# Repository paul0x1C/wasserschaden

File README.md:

# wasserschaden
Project to control solenoid valves over mqtt, check each nodes status in a webpage and via Grafana. 
It allows you to set a location for each node that connects for the first time for easier maintenance.
Nodes equipped with a temperature sensor also send temperature information via mqtt.
To prevent two solenoid valves opening simultaniously, a house enters "locked state". Before opening a solenoid valve,
it checks the lockstate of its house and will only open if the house is in unlocked state.
We log every opening and closing of a valve in order to be able to generate a csv log file, to prove reliability.

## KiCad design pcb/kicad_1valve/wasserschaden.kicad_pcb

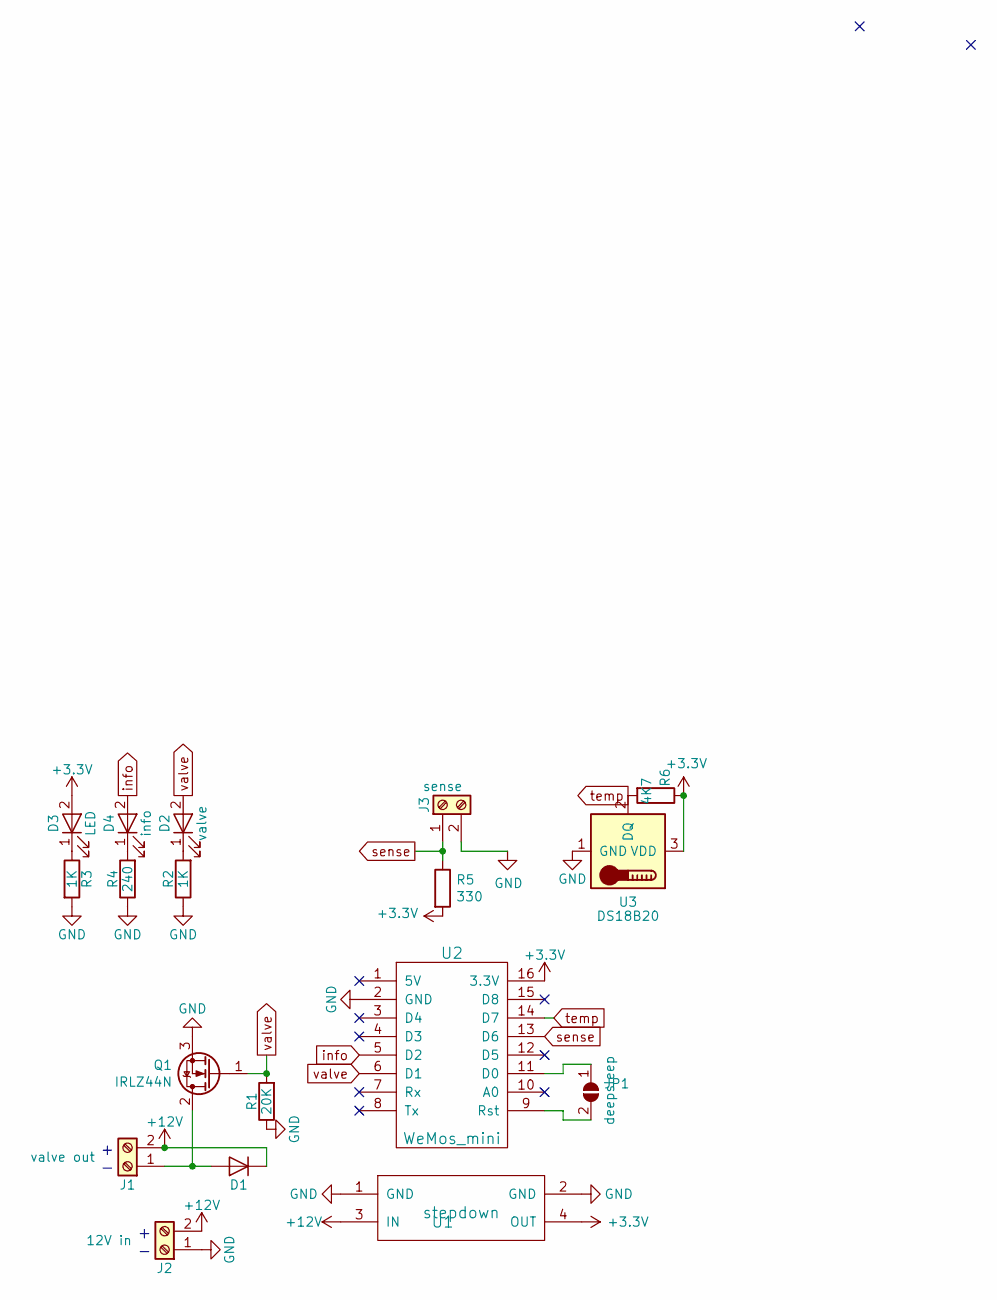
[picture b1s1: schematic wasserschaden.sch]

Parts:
D1: D_SMA_Handsoldering
D2: valve; LED_D3.0mm
D3: LED; LED_D3.0mm
D4: info; LED_D3.0mm
J1: valve out; termina_2pin
J2: 12V in; termina_2pin
J3: sense; termina_2pin
JP1: deepsleep; jumper
Q1: IRLZ44N; TO-220-3_Vertical
R1: 20K; R_0603_HandSoldering
R2, R3: 1K; R_0603_HandSoldering
R4: 240; R_0603_HandSoldering
R5: 330; R_0603_HandSoldering
R6: 4K7; R_0603_HandSoldering
U1: stepdown
U2: WeMos_mini; wemos
U3: DS18B20; temperature_sensor

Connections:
+3V3: D3.2 (A), R5.2, R6.1, U1.4 (OUT), U2.16 (3.3V), U3.3 (VDD)
+12V: D1.1 (K), J1.2, J2.2, U1.3 (IN)
GND: J2.1, J3.2, Q1.3 (S), R1.1, R2.1, R3.2, R4.1, U1.1 (GND), U1.2 (GND), U2.2 (GND), U3.1 (GND); also elsewhere on the board
unnamed 3: D1.2 (A), J1.1, Q1.2 (D); also elsewhere on the board
unnamed: D2.1 (K), R2.2
unnamed: D3.1 (K), R3.1
unnamed: D4.1 (K), R4.2
unnamed: JP1.1 (A), U2.11 (D0)
unnamed: JP1.2 (B), U2.9 (Rst)
info: D4.2 (A), U2.5 (D2)
sense: J3.1, R5.1, U2.13 (D6)
temp: R6.2, U2.14 (D7), U3.2 (DQ)
valve: D2.2 (A), Q1.1 (G), R1.2, U2.6 (D1); also elsewhere on the board

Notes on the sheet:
+ -

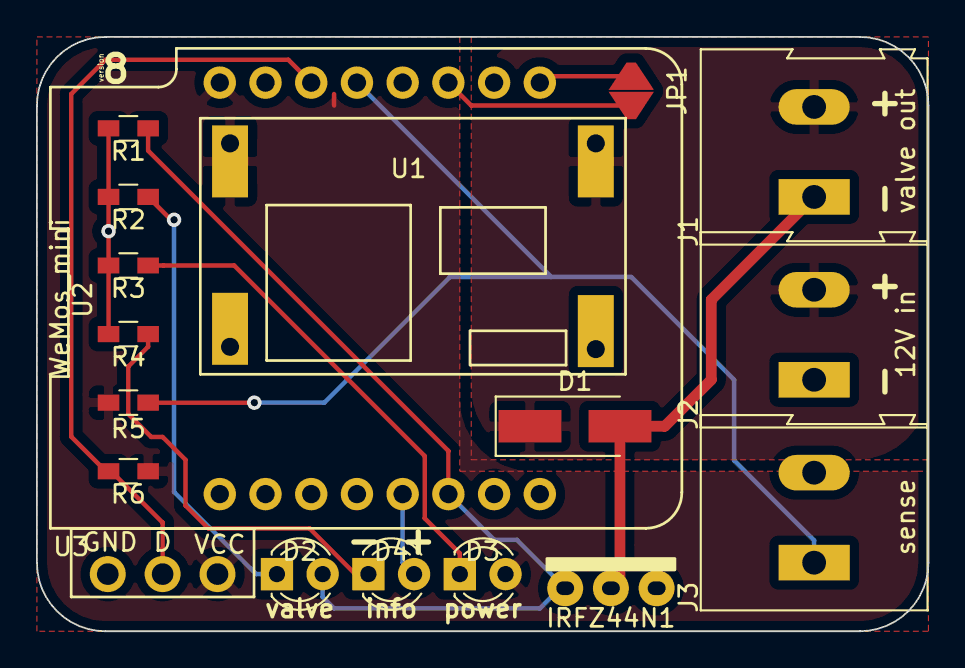
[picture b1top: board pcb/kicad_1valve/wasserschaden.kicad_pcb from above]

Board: 2 copper layers, 49.5 x 33.0 mm, 18 parts (0 on the bottom side), 13 nets.

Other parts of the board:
IRFZ44N1: irlz44n_vertical

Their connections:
GND: IRFZ44N1.1; also elsewhere on the board
unnamed 3: IRFZ44N1.3; also elsewhere on the board
valve: IRFZ44N1.2; also elsewhere on the board

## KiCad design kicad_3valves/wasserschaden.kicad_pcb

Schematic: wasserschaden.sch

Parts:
D1: LED; LED_D3.0mm
D2: info; LED_D3.0mm
D3: v1; LED_D3.0mm
D4: v2; LED_D3.0mm
D5, D7, D8: D_SMA_Handsoldering
D6: v3; LED_D3.0mm
IRFZ44N1, IRFZ44N2, IRFZ44N3: irlz44n_vertical
J1: v1 out; termina_2pin
J2: 12V in; termina_2pin
J3: sense; termina_2pin
J4: v2 out; termina_2pin
J5: v3 out; termina_2pin
JP1: deepsleep; jumper
R1, R3, R4, R6: 1K; R_0603_HandSoldering
R2: 240; R_0603_HandSoldering
R5, R9, R10: 20K; R_0603_HandSoldering
R7: 330; R_0603_HandSoldering
R8: 4K7; R_0603_HandSoldering
U1: stepdown
U2: WeMos_mini; wemos
U3: DS18B20; temperature_sensor

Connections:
+3V3: D1.2 (A), R7.2, R8.1, U1.4, U2.16 (3.3V), U3.3 (VDD)
+12V: D5.1 (K), D7.1 (K), D8.1 (K), J1.2, J2.2, J4.2, J5.2, U1.3
GND: J2.1, J3.2, R1.2, R2.1, R3.1, R4.1, R5.1, R6.1, R9.1, R10.1, U1.1, U1.2, U2.2 (GND), U3.1 (GND); also elsewhere on the board
unnamed: D1.1 (K), R1.1
unnamed: D2.1 (K), R2.2
unnamed: D3.1 (K), R3.2
unnamed: D4.1 (K), R4.2
unnamed 7: D5.2 (A), J1.1; also elsewhere on the board
unnamed: D6.1 (K), R6.2
unnamed 9: D7.2 (A), J4.1; also elsewhere on the board
unnamed 10: D8.2 (A), J5.1; also elsewhere on the board
unnamed: JP1.1 (A), U2.11 (D0)
unnamed: JP1.2 (B), U2.9 (Rst)
info: D2.2 (A), U2.5 (D2)
sense: J3.1, R7.1, U2.13 (D6)
temp: R8.2, U2.14 (D7), U3.2 (DQ)
v1: D3.2 (A), R5.2, U2.6 (D1); also elsewhere on the board
v2: D4.2 (A), R9.2, U2.12 (D5); also elsewhere on the board
v3: D6.2 (A), R10.2, U2.15 (D8); also elsewhere on the board

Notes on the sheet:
+ -

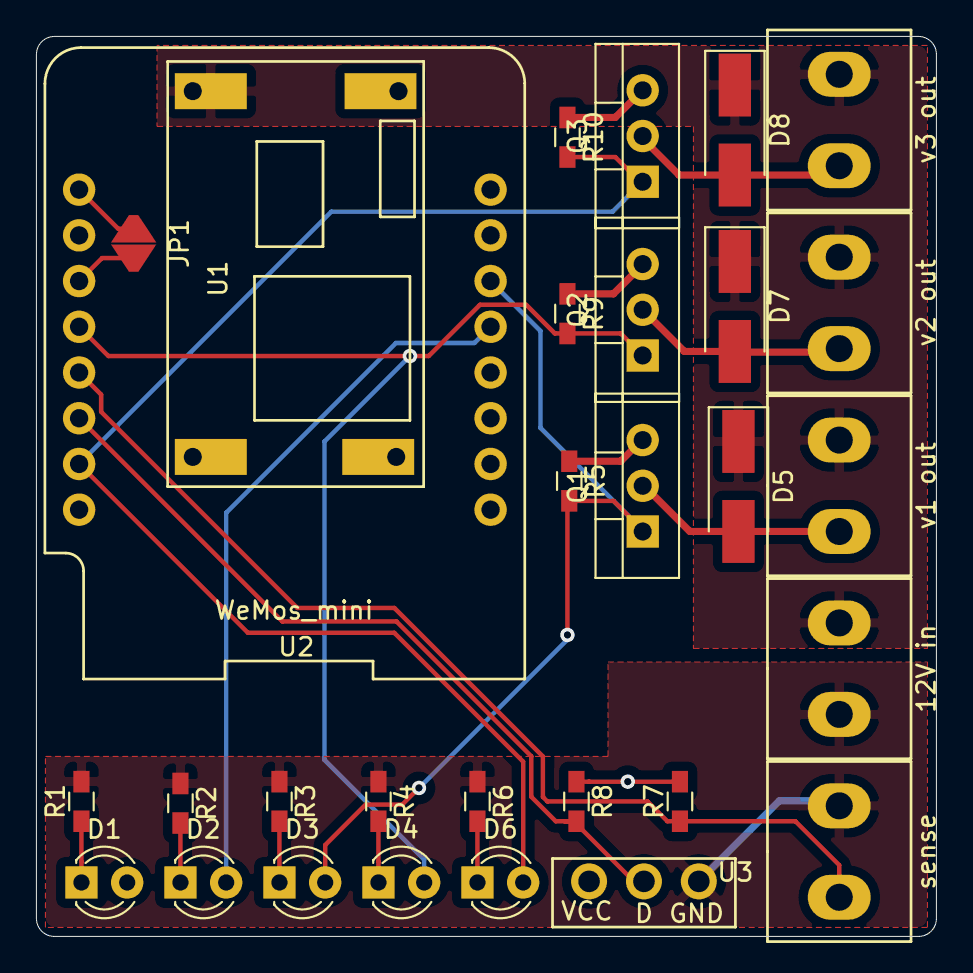
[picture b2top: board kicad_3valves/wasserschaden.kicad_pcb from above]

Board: 2 copper layers, 50.0 x 50.0 mm, 30 parts (0 on the bottom side), 19 nets.

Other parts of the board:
Q1, Q2, Q3: IRLZ44N; TO-220-3_Vertical

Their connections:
GND: Q1.3, Q2.3, Q3.3; also elsewhere on the board
unnamed 7: Q1.2; also elsewhere on the board
unnamed 9: Q2.2; also elsewhere on the board
unnamed 10: Q3.2; also elsewhere on the board
v1: Q1.1; also elsewhere on the board
v2: Q2.1; also elsewhere on the board
v3: Q3.1; also elsewhere on the board

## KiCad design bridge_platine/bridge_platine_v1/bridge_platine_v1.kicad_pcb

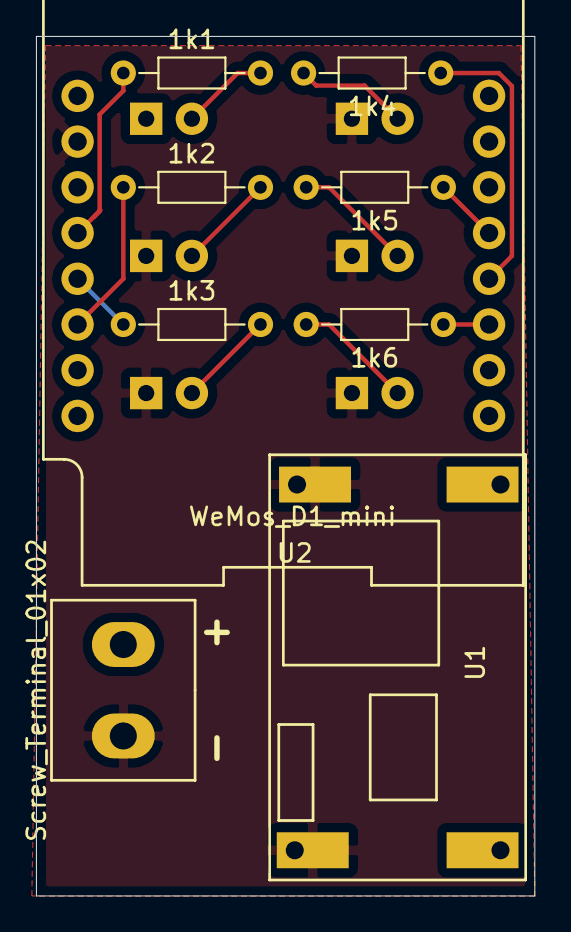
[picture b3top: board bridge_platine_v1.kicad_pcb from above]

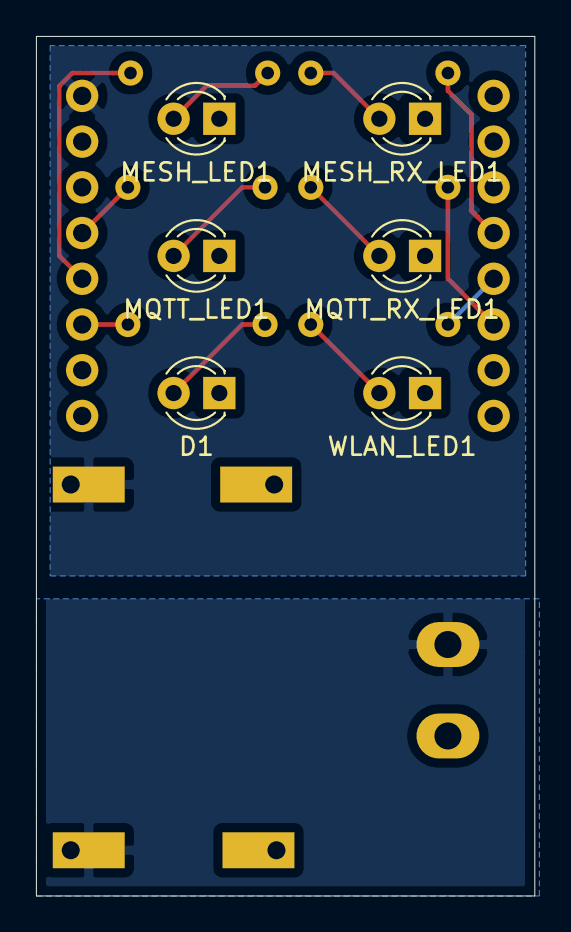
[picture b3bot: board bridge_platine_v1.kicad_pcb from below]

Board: 2 copper layers, 27.7 x 47.8 mm, 15 parts (6 on the bottom side), 15 nets.

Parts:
1k1, 1k2, 1k3, 1k4, 1k5, 1k6: R; R_Axial_DIN0204_L3.6mm_D1.6mm_P7.62mm_Horizontal
D1: POWER_LED; LED_D3.0mm
J1: Screw_Terminal_01x02; termina_2pin
MESH_LED1: LED; LED_D3.0mm
MESH_RX_LED1: LED; LED_D3.0mm
MQTT_LED1: LED; LED_D3.0mm
MQTT_RX_LED1: LED; LED_D3.0mm
U1: stepdown-wasserschaden-cache-2018-10-17-20-35-24; stepdown
U2: WeMos_D1_mini; wemos
WLAN_LED1: LED; LED_D3.0mm

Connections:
+3V3: U1.4, U2.8
GND: D1.1, J1.2, MESH_LED1.1, MQTT_LED1.1, MQTT_RX_LED1.1, U1.1, U1.2, U2.10, WLAN_LED1.1
unnamed: 1k1.1, U2.12
unnamed: 1k1.2, MESH_RX_LED1.2
unnamed: 1k2.1, U2.14
unnamed: 1k2.2, MQTT_RX_LED1.2
unnamed: 1k3.1, U2.13
unnamed: 1k3.2, WLAN_LED1.2
unnamed: 1k4.1, U2.4
unnamed: 1k4.2, MESH_LED1.2
unnamed: 1k5.1, U2.5
unnamed: 1k5.2, MQTT_LED1.2
unnamed: 1k6.1, U2.3
unnamed: 1k6.2, D1.2
unnamed: J1.1, U1.3

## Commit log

2018-08-20 added key.py to gitignore
2018-08-21 better new node handeling and more featurs in node_info.html
2018-08-24 auto refresh
2018-08-26 splited loop.py in timer_loop.py and mqtt_loop.py; fixed automatic mqtt reconnect
2018-08-26 handle advanced ping messages
2018-08-26 added auto refresh options in html
2018-08-26 added autorefresh on/off switch
2018-08-26 added ardunio files to repo
2018-08-26 removed old files
2018-08-29 small fixes
2018-09-22 added log message
2018-09-22 small testing changes
2018-09-26 not sending ping to nodes on first connection
2018-09-26 utf 8 encoding
2018-09-26 db charset
2018-10-01 added status leds
2018-10-01 added caseplans
2018-10-05 implemented status leds
2018-10-10 implemented mqtt custom topics
2018-10-10 custom mqtt topic
2018-10-10 Revert "custom mqtt topic"
    This reverts commit 6651eda04687c469d4528e4c1a76eaf6a2c9868e.
2018-10-10 no flushing when interval=0
2018-10-10 string fuu
2018-10-10 Revert "string fuu"
    This reverts commit 82bc943778d458de0eda92c456a078fc5ff517e1.
2018-10-10 string fck ups
2018-10-13 removed unused functions
2018-10-15 bugfixes
2018-10-17 edit house feature
2018-10-17 less ping spaming when node is diconnected for a long time
2018-10-17 last will
2018-10-17 added kicad files
2018-10-17 queue length indication
2018-10-17 csv export
2018-10-17 clear queue button
2018-10-21 auto updates without stupid refreshes every second ;)
2018-10-21 removed debug console.log()
2018-10-21 fixed decorators
2018-10-22 moved delete options to extra page
2018-10-22 use for new nodes button
2018-10-22 autorefresh when new node is connected
2018-10-22 some cleanup
2018-10-22 new states
2018-10-22 New state colors
2018-10-22 Added BorderColor
2018-10-22 now use two states (connection, physical) instead of one
2018-10-22 mqtt logging
2018-10-22 reactivated reports & node_info
2018-10-23 moved node functions from actions.py to node class
2018-10-24 renamed length to duration
2018-10-24 added deepsleep jumper to schematic &cleanup
2018-10-24 moved caseplans to own folder
2018-10-24 fake mesh for testing base
2018-10-24 working fakemesh with 300 nodes
2018-10-24 removed test.html
2018-10-24 added more log messages
2018-10-26 added next flush info to website
2018-10-26 performance optim.: check only nodes that are not closed and connected
2018-10-26 performance optimization: locks
2018-10-28 css refactored
2018-10-28 added house_id to queue
2018-10-28 added missing session argument
2018-10-28 fixed system module update function
2018-11-01 adjusted alert string size
2018-11-02 added python requirements
2018-11-02 moved node state change to models
2018-11-02 change db to localhost
2018-11-02 react to broadcasts
2018-11-02 performance optimizazion with smarte queue checking
2018-11-02 logging, function names, comments
2018-11-03 comments, logging
2018-11-03 new_node_flat now selectable for each house
2018-11-03 added telegrambot
2018-11-03 changed length to duration
2018-11-03 added missing >
2018-11-03 prevent houses from not beeing unlocked
2018-11-05 small adjustments
2018-11-05 Added representers
2018-11-05 now using new representers
2018-11-08 moved node state change to timer_loop, added workaround for relationship bug
2018-11-08 added watchdog
2018-11-08 added watchdog, fixed bug with custom bridge topics
2018-11-09 moved house unlocking to mqtt loop
2018-11-09 prevent requeueing of nodes
2018-11-09 added jumper to pcb
2018-11-10 added sense jumper to schematic
2018-11-10 small optimizzations
2018-11-10 added priority levels to add_alert function
2018-11-10 added alert priority to telegram bot
2018-11-11 Update LICENSE
2018-11-12 made gateway pingable
2018-11-12 removed test line that broke priority checking
2018-11-12 added 'not conneceted' msg haneling
2018-11-12 cleaned up kicad dir
2018-11-12 fakemesh with 6 different gateways
2018-11-12 added sense input
2018-11-12 major pcb rearangement
2018-11-12 chagned gateway_status to int, added alert emojis, moved chat_id to key.py
2018-11-12 added msg length limit for telegram messages
2018-11-12 changed datetime string representation on website
2018-11-12 combine repeating alerts
2018-11-12 created ping function for Node, more bot options
2018-11-12 better bot menu
2018-11-12 added alert on requeueing of nodes
2018-11-13 added button selection for priority levels
2018-11-13 send not connected from node, when node is not connected
2018-11-13 pcb redesigen
2018-11-28 enabled watchdog, changed flushtime, reboot if bridge is not found
2018-11-28 added function to calc average resp. time
2018-12-01 added log function, globally replaced logger
2018-12-01 fixed timer_loop failing when last_flush is not set
2018-12-05 added led test on boot
2018-12-06 commit session after locking house
2018-12-06 only process que if qateway is connected
2018-12-06 added temperature sensor
2018-12-08 added R values, improved stepdown footprint, rerouted resistors
2019-01-10 added temperature and water sense, updated communication
2019-01-13 updated fakemesh to new communication
2019-01-13 nicer silkscreen
2019-01-13 updated communication, added temperature sensror, set root node
2019-01-13 don't spam gateway pings
2019-01-17 use utc time in db
2019-01-17 connection state names changed
2019-01-17 better gateway state handeling
2019-01-24 fixed deleting and moving nodes
2019-01-24 Created a readme file with project overview
2019-01-24 changed wording
2019-01-31 run one wire on the right pin ^^
2019-01-31 added 12V zone, made screw terminals interlockable
2019-02-07 added more comments
2019-02-08 first smd version
2019-02-08 v4 export
2019-02-14 small rerouting
2019-02-24 fixed minor mistakes
2019-02-25 fixed time stuff
2019-02-25 added node stats for houses
2019-02-25 added watchdog, changed mqtt ip, set wifi mode & channel
2019-02-25 formating fix
2019-02-27 added tempeature polling
2019-02-27 prevent temperature request spamming
2019-02-27 fixed circular dep. error when deleting houses
2019-04-09 pcb v7
2019-04-09 multi gateway support
2019-04-09 added temperature sensor reset option
2019-04-09 removed small important mistakes
2019-04-16 fixed traces near pads
2019-04-16 removed old zip
2019-05-06 added 3d design for valves on HT pipe
2019-05-10 added colors
2019-05-10 added pinout.txt
2019-05-11 moved sense pin from D3 to D6 since D3 must be HIGH on boot
2019-05-11 copied v7
2019-05-11 fixed D3 in current pcb
2019-05-11 cleaned up old files and replaced main pcb with smd version
2019-05-11 changed D3 to D6
2019-07-02 changed logging level
2019-07-05 reset bridge after 30m without a mqtt msg
2019-07-16 moved kicad files
2019-07-16 make use of net labels more often
2019-07-17 first routing atempt for 3 valve board
2019-07-17 fancy routing for 3 valve board
2019-08-01 set has_temerature_sensor to false when nodes don't have a sensor
2019-08-01 fixed important typo
2019-08-06 only set last_connection_change when connection state really changed
2019-08-06 attempts instead of attemps… oof
2019-08-06 set alerts to sent instead of deleting them
2019-08-12 better state change handeling
2019-08-12 move flush init to own function
2019-08-12 flush now button
2019-08-12 add flush now button
2019-08-12 fixed gateway offline loglevel
2019-08-12 3 valve pcb
2019-08-12 don't reset state_time for changes between c-state 2 and 3
2019-09-23 fix connecton_state timer not resetting
2019-09-23 broadcast ping before initiating flush
2019-09-28 ignore gerber, drill and zip files
2019-09-28 round corners
2019-09-29 version 8
2019-09-29 fixed terminal spacing
2019-09-29 reboot when bridge is unreachable for to long
2019-09-29 PCB for bridge
2019-10-03 added missing track
2019-10-12 add sense notifications and visualization
2019-10-12 add notifications for nodes going offline or online
2019-10-12 take db wrapper from actions.py
2019-10-12 add limit parameter
2019-10-12 add state emojis
2019-10-12 store timestamps with milliseconds
2019-10-12 add status command
2019-10-14 use propper symbol and footprint for irlz44n
2019-10-28 adapted LED holes for bridge PCB v1
2019-10-29 change gateway to bridge
2019-10-29 rename gatway to bridge, cleanup state-change
2019-10-29 don't report node back online, when it's just waiting for ping
2019-11-01 rename gateway to bridge, reject repeated open msgs
2019-11-01 set defaults, fix division by zero in response time calculation
2019-11-01 prevent reapeated sense alerts, add stop-sense alert
2019-11-01 only send temp polls to connected nodes
2019-11-01 fix ping, automaticlly send sense msg when detecting water
2019-11-08 close valve when detecting water
2019-11-13 add access control to buttons, more infos for nodes
2019-11-13 rename has_sense_pin, add initial_connection parameter for nodes
2019-11-13 only send sense alerts for nodes connected since >2m and set has_sense_plate=True otherwise
2019-11-13 add more infos and options to /list_houses
2019-11-13 automaticly add buttons for objects mentoined in alerts
2019-12-09 set initial_connection time when nodes connect
2019-12-09 add more buttons and clean_alerts command
2019-12-09 send alerts when bridge (re)connects to mqtt
2019-12-09 remove not used file
2019-12-09 add report page
2020-01-08 moved pcbs to own folder
